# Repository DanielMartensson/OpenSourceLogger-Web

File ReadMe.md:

# OpenSourceLogger

This software creates a web application with Spring Boot and with this web application you can control and measure analog inputs and outputs and 
store them into a MySQL database.

# Features

* 4 Analog inputs of 12-bit
* 2 Analog inputs of 16-bit
* 3 Analog inputs of 16-bit differential
* 9 PWM control outputs
* 6 Digital inputs
* 3 Analog outputs of 12-bit
* Circuit protection from high voltage
* Spring Security Login
* MySQL database
* USB Camera view (Does not work with Raspberry Pi)
* Plotting functionality
* SMTP alarm functionality
* CSV generation of measurements
* Connect with RX and TX from Raspberry Pi pins
* Save unsaved database measurement for later if database might be slow for a moment
* Close down PWM and analog outputs when stop logging or alarm goes of

With this user view, you can control PWM, DAC, read ADC and logging digital inputs online over the web.
Set an alarm and calibration of a special sensor you want to use. Store all data inside the database. 
Then later you can bring the measurement back to a plot. Notice that you can close down the web browser while you logging.
It will continue to sample in a separate thread. 

This is made in KiCad. I have drag all the tracks on the board by my self. No auto-routing here.

I have solder all components by my self.

I have solder this microcontroller by hand. 

Applied inside a metallic box. Here I'm using Raspberry Pi to communicate with the board.
You can use a regular computer as well, as long you have a USB to serial converter, e.g `USB/UART converter FTDI FT232` where you connect `RXD -> TX` and `TXD -> RX` on the board.

# How to install - Ubuntu user

1. Install Java 11, Maven, NodeJS

Java 11
```
sudo apt-get install openjdk-11-jdk
```

Maven
```
sudo apt-get install maven
```

NodeJS
```
curl -sL https://deb.nodesource.com/setup_lts.x | sudo -E bash -
sudo apt-get install -y nodejs
```

2. Begin first to install MySQL Community Server

```
sudo apt-get install mysql-server
```

3. Then create a user e.g `myUser` with the password e.g `myPassword`

Login and enter your `sudo` password or mysql `root` password
```
sudo mysql -u root -p
```

Create user with the host `%` <-- That's important if you want to access your server from other computers.
```
CREATE USER 'myUser'@'%' IDENTIFIED BY 'myPassword';
```

Set the privileges to that user
```
GRANT ALL PRIVILEGES ON *.* TO 'myUser'@'%';
```

4. Change your MySQL server so you listening to your LAN address

Open this file
```
/etc/mysql/mysql.conf.d/mysqld.conf
```

And change this
```
bind-address            = 127.0.0.1
```

To your LAN address where the server is installed on e.g
```
bind-address            = 192.168.1.34
```

Then restart your MySQL server
```
sudo /etc/init.d/mysql restart
```

If you don't know your LAN address, you can type in this command in linux `ifconfig` in the terminal

5. Download `OpenSourceLogger`

Download the `OpenSourceLogger` and change the `application.properties` in the `/src/main/resources` folder.
Here you can set the configuration for your database IP address, user and password. Here set the address of your `Outlook` account.
The `service.MailService.from` must be the same as `configuration.MailConfiguration.username`.

```
# Database
spring.jpa.show-sql=true
spring.jpa.hibernate.ddl-auto=update
spring.jpa.properties.hibernate.dialect=org.hibernate.dialect.MySQL5Dialect
spring.datasource.url=jdbc:mysql://yourIPAddressOfTheServerWhereMySQLIsInstalled:3306/OpenSourceLogger?createDatabaseIfNotExist=true&serverTimezone=CET
spring.datasource.username=myUser
spring.datasource.password=myPassword

# Mail - Transmitter
configuration.MailConfiguration.host=smtp.office365.com
configuration.MailConfiguration.port=587
configuration.MailConfiguration.username=yourOutlookAccount@outlook.com
configuration.MailConfiguration.password=yourOutlookPassword

# Mail - Receiver
service.MailService.subject=Alarm Message Subject Title
service.MailService.from=yourOutlookAccount@outlook.com

# Login
spring.security.user.name=myUser
spring.security.user.password=myPassword
```

6. Pack this project and run

First stand inside of the folder `OpenSourceLogger` and write inside your terminal
```
mvn package -Pproduction
```

7. Starting the application

Now a JAR file is created inside the `OpenSourceLogger/target` folder. 

You can start `opensourcelogger-1.0-SNAPSHOT.jar`. First plugin your Serial UART into your USB port first, then write. 

```
sudo java -jar opensourcelogger-1.0-SNAPSHOT.jar
```

Once the application is started. You can then enter the web application e.g.

```
http://192.168.1.35:8080
```
Notice that there is no `https`, only `http`.

# Deploy onto Raspberry Pi

Notice that camera won't work on Raspberry Pi due to the latest library from [Sarox](https://github.com/sarxos/webcam-capture) cannot support Raspberry Pi 4B. But you can 
do everything else. If you want to work with this camera stuff inside `OpenSourceLogger`, please go to `CameraThread.java` class and begin to explore how to solve that problem.

Anyway! Once you got `opensourcelogger-1.0-SNAPSHOT.jar` ready, you can send it to your Raspberry Pi.

```
sudo scp opensourcelogger-1.0-SNAPSHOT.jar pi@RaspberryPiIPAddress:/The/Place/You/Want/The/Jar/File/To/Be/Saved
```

Example:

```
sudo scp opensourcelogger-1.0-SNAPSHOT.jar pi@192.168.1.35:/home/pi
```

Then open `rc.local`

```
sudo nano /etc/rc.local
```

And place these line above `exit 0`

```
cd /The/Path/To/Where/The/Jar/File/Is/Placed
sudo java -jar opensourcelogger-1.0-SNAPSHOT.jar &
```
Or if you want to specify the Java Heap Space for e.g `1024` Megabyte. Can be good if you want to download `.csv` data from the database.
```
cd /The/Path/To/Where/The/Jar/File/Is/Placed
sudo java -Xmx1024m -jar opensourcelogger-1.0-SNAPSHOT.jar &
```

Important with `&`, else Raspberry Pi is going to get stuck there with the `Spring Boot` terminal at the startup.

Then you need to enable `Serial` in Raspberry Pi.
```
sudo raspi-config
```
Then enable `Serial`. It's at the same page where you enable `SSH`, `VNC`, `I2C` etc. 
Once you found `Serial` option, answer `NO` to the question about login shell.
Then answer `YES` to the question about serial hardware port.
Then when you exit the `raspi-config`, it will ask you if you want to reboot, press `YES`

Now your `OpenSourceLogger` will starts automatically. Select the port `ttyS0` in `Device settings` at `OpenSourceLogger` and save the configuration
inside the database. `ttyS0` is the `RX` and `TX` pins of the Raspberry Pi. Done!

# Build an own board

Download `DAC ADC PWM IO - Board Schematic` and `DAC ADC PWM IO - STM32 Code` folder.
Inside the `DAC ADC PWM IO - Board Schematic` folder, there is a `.csv` Bill Of Materials list with article numbers from Mouser Electronics. 
I have been using `KiCad` to create these files and I used `https://jlcpcb.com` to give them the `gerber` files from the `DAC ADC PWM IO - Board Schematic` folder.

To program the board, use a `ST-LINK-V2` programmer to program the board with `STM32CubeIDE 1.5.0`.

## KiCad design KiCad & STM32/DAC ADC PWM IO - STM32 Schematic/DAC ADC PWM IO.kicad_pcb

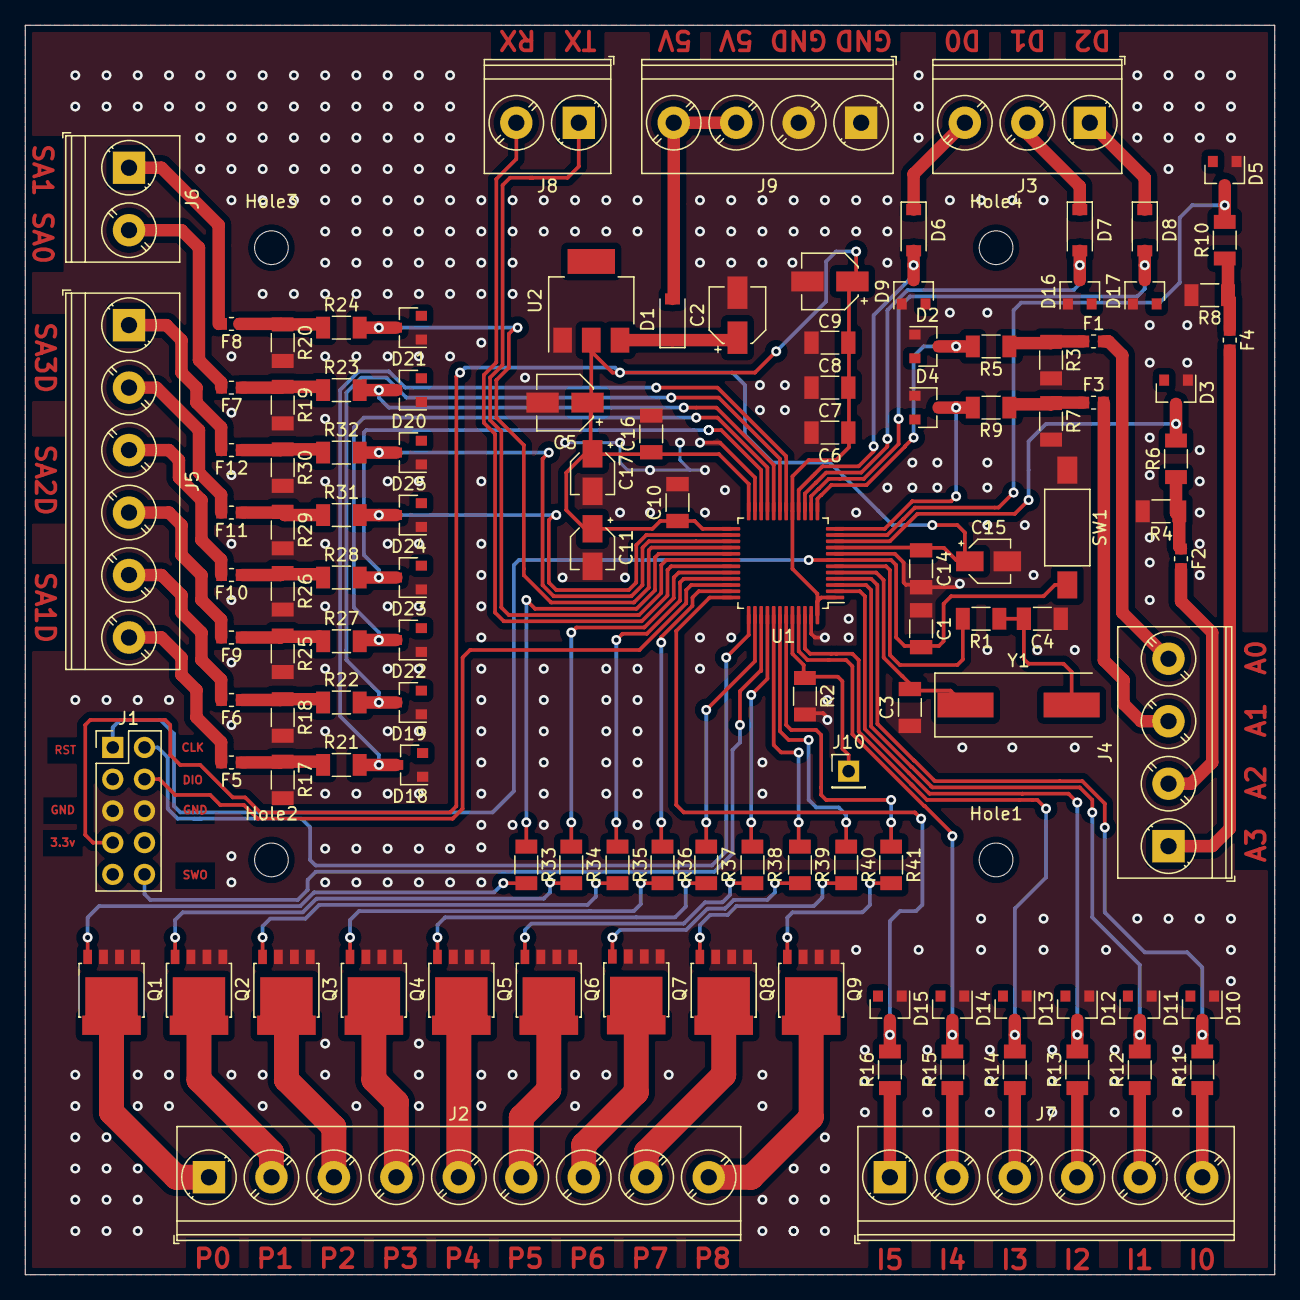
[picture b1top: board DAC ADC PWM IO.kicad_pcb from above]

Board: 2 copper layers, 100.0 x 100.0 mm, 120 parts (0 on the bottom side), 95 nets.

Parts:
C1, C6, C7, C8: 100nF; C_1206_3216Metric
C2, C5: 10uF; CP_Elec_4x5.3
C3, C4: 16pF; C_1206_3216Metric
C9: 4.7uF; CP_Elec_4x5.4
C10, C14, C16: 10nF; C_1206_3216Metric
C11, C15, C17: 1uF; CP_Elec_3x5.4
D1: MBR130T1G; D_SOD-123
D2, D3, D4, D5, D9, D10, D11, D12, D13, D14, D15, D16, D17, D18, D19, D20, D21, D22, D23, D24, D25: BZX84C3V6LT1G; D_SOT-23_ANK
D6, D7, D8: BAT54T1G; D_SOD-123
F1, F2, F3, F4, F5, F6, F7, F8, F9, F10, F11, F12: Polyfuse; Fuse_0603_1608Metric
Hole1, Hole2, Hole3, Hole4: MountingHole_2.7mm
J1: Debugger; PinHeader_2x05_P2.54mm_Vertical
J2: PWM; TerminalBlock_Phoenix_PT-1,5-9-5.0-H_1x09_P5.00mm_Horizontal
J3: DAC; TerminalBlock_Phoenix_PT-1,5-3-5.0-H_1x03_P5.00mm_Horizontal
J4: 4-20mA 12-bit; TerminalBlock_Phoenix_PT-1,5-4-5.0-H_1x04_P5.00mm_Horizontal
J5: 4-20mA 16-bit Differential; TerminalBlock_Phoenix_PT-1,5-6-5.0-H_1x06_P5.00mm_Horizontal
J6: 4-20mA 16-bit; TerminalBlock_Phoenix_PT-1,5-2-5.0-H_1x02_P5.00mm_Horizontal
J7: Input; TerminalBlock_Phoenix_PT-1,5-6-5.0-H_1x06_P5.00mm_Horizontal
J8: UART; TerminalBlock_Phoenix_PT-1,5-2-5.0-H_1x02_P5.00mm_Horizontal
J9: PWR; TerminalBlock_Phoenix_PT-1,5-4-5.0-H_1x04_P5.00mm_Horizontal
J10: Conn_01x01_MountingPin; PinHeader_1x01_P2.54mm_Vertical
Q1, Q2, Q3, Q4, Q5, Q6, Q7, Q8, Q9: BUK9Y43-60E,115; LFPAK56
R1: 620; R_1206_3216Metric
R2, R11, R12, R13, R14, R15, R16: 10k; R_1206_3216Metric
R3, R4, R7, R8, R17, R18, R19, R20, R25, R26, R29, R30: 150; R_1206_3216Metric
R5, R6, R9, R10, R21, R22, R23, R24, R27, R28, R31, R32: 2k; R_1206_3216Metric
R33, R34, R35, R36, R37, R38, R39, R40, R41: 1k; R_1206_3216Metric
SW1: SW_Push; SW_SPST_FSMSM
U1: STM32F373CCT6; LQFP-48_7x7mm_P0.5mm
U2: LM1117-3.3; SOT-223
Y1: 16Mhz, 18pF; Crystal_SMD_HC49-SD

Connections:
+3V3: C5.1, C6.1, C7.1, C8.1, C9.1, C10.1, C11.1, C14.1, C15.1, C16.1, C17.1, J1.7, U1.1, U1.9, U1.17, U1.24, U1.25, U1.48, U2.2
+5V: D1.2, J9.3, J9.4
/ADC/ADC0: F1.2, J4.4
/ADC/ADC1: F3.2, J4.3
/ADC/ADC2: F2.2, J4.2
/ADC/ADC3: F4.2, J4.1
/BOOT0: J10.1, R2.1, U1.44
/DAC/DAC0: D6.1, J3.3
/DAC/DAC1: D7.1, J3.2
/DAC/DAC2: D8.1, J3.1
/INPUT/INPUT0: J7.6, R11.1
/INPUT/INPUT1: J7.5, R12.1
/INPUT/INPUT2: J7.4, R13.1
/INPUT/INPUT3: J7.3, R14.1
/INPUT/INPUT4: J7.2, R15.1
/INPUT/INPUT5: J7.1, R16.1
/NRST: C1.2, J1.1, SW1.2, U1.7
/PA0: D3.1, R6.2, U1.10
/PA1: D5.1, R10.2, U1.11
/PA2: D4.1, R9.2, U1.12
/PA3: D2.1, R5.2, U1.13
/PA4: D8.2, D17.1, U1.14
/PA5: D7.2, D16.1, U1.15
/PA6: D6.2, D9.1, U1.16
/PA8: R33.1, U1.29
/PA9: J8.1, U1.30
/PA10: J8.2, U1.31
/PA11: R34.1, U1.32
/PA12: R35.1, U1.33
/PA13: J1.4, U1.34
/PA14: J1.2, U1.37
/PA15: R37.1, U1.38
/PB0: D18.1, R21.2, U1.18
/PB1: D19.1, R22.2, U1.19
/PB2: D20.1, R23.2, U1.20
/PB3: J1.10, U1.39
/PB4: R38.1, U1.40
/PB5: R39.1, U1.41
/PB6: R40.1, U1.42
/PB7: R41.1, U1.43
/PB8: D14.1, R15.2, U1.45
/PB9: D13.1, R14.2, U1.46
/PB14: D24.1, R31.2, U1.26
/PB15: D25.1, R32.2, U1.27
/PC13: D12.1, R13.2, U1.2
/PC14: D11.1, R12.2, U1.3
/PC15: D10.1, R11.2, U1.4
/PD8: D21.1, R24.2, U1.28
/PE8: D22.1, R27.2, U1.21
/PE9: D23.1, R28.2, U1.22
/PF0: C3.2, U1.5, Y1.1
/PF1: R1.2, U1.6
/PF6: R36.1, U1.35
/PF7: D15.1, R16.2, U1.36
/PWM/PWM0: J2.1, Q1.5
/PWM/PWM1: J2.2, Q2.5
/PWM/PWM2: J2.3, Q3.5
/PWM/PWM3: J2.4, Q4.5
/PWM/PWM4: J2.5, Q5.5
/PWM/PWM5: J2.6, Q6.5
/PWM/PWM6: J2.7, Q7.5
/PWM/PWM7: J2.8, Q8.5
/PWM/PWM8: J2.9, Q9.5
/SDADC/SDADC0M: F6.2, J5.5
/SDADC/SDADC0P: F5.2, J5.6
/SDADC/SDADC1: F7.2, J6.2
/SDADC/SDADC2: F8.2, J6.1
/SDADC/SDADC2M: F10.2, J5.3
/SDADC/SDADC2P: F9.2, J5.4
/SDADC/SDADC3M: F12.2, J5.1
/SDADC/SDADC3P: F11.2, J5.2
GND: C1.1, C2.2, C3.1, C4.1, C5.2, C6.2, C7.2, C8.2, C9.2, C10.2, C11.2, C14.2, C15.2, C16.2, C17.2, D2.2, D3.2, D4.2, D5.2, D9.2, D10.2, D11.2, D12.2, D13.2, D14.2, D15.2, D16.2, D17.2, D18.2, D19.2, D20.2, D21.2, D22.2, D23.2, D24.2, D25.2, J1.5, J1.6, J9.1, J9.2, Q1.1, Q1.2, Q1.3, Q2.1, Q2.2, Q2.3, Q3.1, Q3.2, Q3.3, Q4.1, Q4.2, Q4.3, Q5.1, Q5.2, Q5.3, Q6.1, Q6.2, Q6.3, Q7.1, Q7.2, Q7.3, Q8.1, Q8.2, Q8.3, Q9.1, Q9.2, Q9.3, R2.2, R3.2, R4.2, R7.2, R8.2, R17.2, R18.2, R19.2, R20.2, R25.2, R26.2, R29.2, R30.2, SW1.1, U1.8, U1.23, U1.47, U2.1
unnamed: C2.1, D1.1, U2.3
unnamed: C4.2, R1.1, Y1.2
unnamed: F1.1, R3.1, R5.1
unnamed: F2.1, R4.1, R6.1
unnamed: F3.1, R7.1, R9.1
unnamed: F4.1, R8.1, R10.1
unnamed: F5.1, R17.1, R21.1
unnamed: F6.1, R18.1, R22.1
unnamed: F7.1, R19.1, R23.1
unnamed: F8.1, R20.1, R24.1
unnamed: F9.1, R25.1, R27.1
unnamed: F10.1, R26.1, R28.1
unnamed: F11.1, R29.1, R31.1
unnamed: F12.1, R30.1, R32.1
unnamed: Q1.4, R33.2
unnamed: Q2.4, R34.2
unnamed: Q3.4, R35.2
unnamed: Q4.4, R36.2
unnamed: Q5.4, R37.2
unnamed: Q6.4, R38.2
unnamed: Q7.4, R39.2
unnamed: Q8.4, R40.2
unnamed: Q9.4, R41.2

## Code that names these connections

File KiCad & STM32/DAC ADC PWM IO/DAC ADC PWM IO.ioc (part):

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Mcu.Name=STM32F373C(8-B-C)Tx
Mcu.Package=LQFP48
Mcu.UserName=STM32F373CCTx
PA0.Mode=IN0
PA0.Signal=ADC1_IN0
PA1.Mode=IN1
PA1.Signal=ADC1_IN1
PA10.Mode=Asynchronous
PA10.Signal=USART1_RX
PA11.Signal=S_TIM5_CH2
PA12.Signal=S_TIM5_CH3
PA13.Mode=Trace_Asynchronous_SW
PA13.Signal=SYS_JTMS-SWDIO
PA14.Mode=Trace_Asynchronous_SW
PA14.Signal=SYS_JTCK-SWCLK
PA15.Signal=S_TIM2_CH1_ETR
PA2.Mode=IN2
PA2.Signal=ADC1_IN2
PA3.Mode=IN3
PA3.Signal=ADC1_IN3
PA4.Signal=COMP_DAC11_group
PA5.Signal=COMP_DAC12_group
PA6.Signal=COMP_DAC21_group
PA8.Signal=S_TIM5_CH1_ETR
PA9.Mode=Asynchronous
PA9.Signal=USART1_TX
PB0.Mode=IN6-Differential
PB0.Signal=SDADC1_AIN6P
PB1.Mode=IN6-Differential
PB1.Signal=SDADC1_AIN6M
PB14.Mode=IN8-Differential
PB14.Signal=SDADC3_AIN8P
PB15.Mode=IN8-Differential
PB15.Signal=SDADC3_AIN8M
PB2.Mode=IN4-Single-Ended zero reference
PB2.Signal=SDADC1_AIN4P
PB3.Mode=Trace_Asynchronous_SW
PB3.Signal=SYS_JTDO-TRACESWO
PB4.Signal=S_TIM3_CH1
PB5.Signal=S_TIM3_CH2
PB6.Signal=S_TIM4_CH1
PB7.Signal=S_TIM4_CH2
PB8.GPIOParameters=GPIO_PuPd,GPIO_Label
PB8.GPIO_Label=INPUT 4
PB8.GPIO_PuPd=GPIO_PULLDOWN
PB8.Signal=GPIO_Input
PB9.GPIOParameters=GPIO_PuPd,GPIO_Label
PB9.GPIO_Label=INPUT 3
PB9.GPIO_PuPd=GPIO_PULLDOWN
PB9.Signal=GPIO_Input
PC13.GPIOParameters=GPIO_PuPd,GPIO_Label
PC13.GPIO_Label=INPUT 2
PC13.GPIO_PuPd=GPIO_PULLDOWN
PC13.Signal=GPIO_Input
PC14-OSC32_IN.GPIOParameters=GPIO_PuPd,GPIO_Label
PC14-OSC32_IN.GPIO_Label=INPUT 1
PC14-OSC32_IN.GPIO_PuPd=GPIO_PULLDOWN
PC14-OSC32_IN.Signal=GPIO_Input
PC15-OSC32_OUT.GPIOParameters=GPIO_PuPd,GPIO_Label
PC15-OSC32_OUT.GPIO_Label=INPUT 0
PC15-OSC32_OUT.GPIO_PuPd=GPIO_PULLDOWN
PC15-OSC32_OUT.Signal=GPIO_Input
PD8.Mode=IN6-Single-Ended zero reference
PD8.Signal=SDADC3_AIN6P
PE8.Mode=IN8-Differential
PE8.Signal=SDADC1_AIN8P
PE9.Mode=IN8-Differential
PE9.Signal=SDADC1_AIN8M
PF0-OSC_IN.Mode=HSE-External-Oscillator
PF0-OSC_IN.Signal=RCC_OSC_IN
PF1-OSC_OUT.Mode=HSE-External-Oscillator
PF1-OSC_OUT.Signal=RCC_OSC_OUT
PF6.Signal=S_TIM4_CH4
PF7.GPIOParameters=GPIO_PuPd,GPIO_Label
PF7.GPIO_Label=INPUT 5
PF7.GPIO_PuPd=GPIO_PULLDOWN
PF7.Signal=GPIO_Input
RCC.HSEPLLFreq_Value=16000000
RCC.HSE_VALUE=16000000
RCC.SYSCLKFreq_VALUE=16000000
RCC.SYSCLKSource=RCC_SYSCLKSOURCE_HSE
board=custom

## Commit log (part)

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2020-07-12 New init
2020-07-17 Update - Ready for testing
2020-08-17 New update
2020-10-05 Changed from GAIN_TWO to GAIN_ONE
2020-10-05 Changes insert for MySQL
2020-10-05 Batch sampling now
2020-10-05 New delete notification for Stack Overflow
2020-10-06 Fixed Download button
2020-10-06 Changed LocalDate to LocalDateTime
2020-10-06 Update all
2020-10-06 Implementing milliseconds in Entity
2020-10-06 Updated from GitHub
2020-10-06 Update MySQL view
2020-10-06 Correct order of data samples now
2020-10-06 Update Download Button
2020-11-09 News
2020-11-09 News and updates
2020-11-09 Update with explanations
2020-12-22 Bump ini from 1.3.5 to 1.3.8
    Bumps [ini](https://github.com/isaacs/ini) from 1.3.5 to 1.3.8.
    - [Release notes](https://github.com/isaacs/ini/releases)
    - [Commits](https://github.com/isaacs/ini/compare/v1.3.5...v1.3.8)
2020-12-22 Uploaded STM32 board and code
2020-12-23 Solution for Raspberry Pi
2020-12-23 Update for raspberry pi camera
2020-12-23 Update ish...
2020-12-23 Upload STM32 board and code
2020-12-23 Update instructions how to build the board
2020-12-23 Removed picture
2020-12-23 Update box picture
2020-12-23 Add Board PCB schematics and code
2020-12-23 Added more information how to enable S0
2020-12-23 Added STM32 files
2020-12-23 Misspell
2020-12-24 Fixed indexing
2020-12-24 Update and clean up
2020-12-25 Renamed
2020-12-25 Update. Found bugs. Solved issues...
2020-12-25 Removed a space
2020-12-25 For to From
2020-12-25 More information
2020-12-28 Found a better way to stop logging directly
2020-12-29 When we delete job, the corresponding data will also be removed
2020-12-29 New UI view
2020-12-29 Solved an issue about couted pulses
2020-12-29 Vaadin Update
2020-12-29 Clears array before receiving data
2020-12-29 Clear all int arrays
2020-12-29 16-bit ADC applied for single
2020-12-29 Changed 0-20mA to 0-22mA because I'm using 150 Ohm resistor
2020-12-30 New calibration manual
2020-12-30 Better size of the images
2021-01-02 Lower baudrate from 115200 to 9600
2021-01-03 Better communication with STM32
2021-01-03 Got a UIDetechedException
2021-01-03 When the alarm is active, then we have recieve the stopSignal variable to true
2021-01-03 Removes the curly blocks from single if-statement
2021-01-05 Offline sampling applied
2021-01-05 Implement safety features and database connection check
2021-01-05 Update dependencies
2021-01-05 Better code and easier to understand
2021-01-05 Update alarmService and calibrationService
2021-01-05 Possible to show one or multiple chart series now
2021-01-09 Big update 2 - Faster Database reading
2021-01-10 Update with step
2021-01-10 Euler simulation for first order state space equation, as filter
2021-01-10 Done with better MySQL reading
2021-01-10 Changed "Step index" to "Step index(plot only)"
2021-01-10 Renamed DateTime to LocalDateTime
2021-01-10 Update Vaadin
2021-01-10 Update to Long
2021-01-10 x -> ADC
2021-01-10 Change initial Euler filtering to 1.0
2021-01-10 Step index cannot be larger than last index
2021-01-10 Implements counter how many times we can write to database
2021-01-11 Update - Found a bug
2021-01-11 Better moving average
2021-01-11 Use static string fields as names for the fields in Data class
2021-01-12 Update class path
2021-01-13 Added Notification "Out of memory"
2021-01-13 Add comment to database and job
2021-01-13 Add comment field to JobView
2021-02-11 Bump apexcharts from 3.20.2 to 3.24.0
    Bumps [apexcharts](https://github.com/apexcharts/apexcharts.js) from 3.20.2 to 3.24.0.
    - [Release notes](https://github.com/apexcharts/apexcharts.js/releases)
    - [Commits](https://github.com/apexcharts/apexcharts.js/commits)
2021-02-23 Added @Transactional for deleteByJobName(String jobName)
    Got the error "No EntityManager with actual transaction available for current thread - cannot reliably process 'remove' call"
2021-02-24 Added a Query for deleteByJobName
    I hope this should be faster!
2021-04-19 Bump vaadin.version from 14.4.5 to 19.0.5
    Bumps `vaadin.version` from 14.4.5 to 19.0.5.
    Updates `vaadin-bom` from 14.4.5 to 19.0.5
    Updates `vaadin-maven-plugin` from 14.4.5 to 19.0.5
2021-04-20 Bump ssri from 6.0.1 to 6.0.2
    Bumps [ssri](https://github.com/npm/ssri) from 6.0.1 to 6.0.2.
    - [Release notes](https://github.com/npm/ssri/releases)
    - [Changelog](https://github.com/npm/ssri/blob/v6.0.2/CHANGELOG.md)
    - [Commits](https://github.com/npm/ssri/compare/v6.0.1...v6.0.2)
2021-04-22 Bump elliptic from 6.5.3 to 6.5.4
    Bumps [elliptic](https://github.com/indutny/elliptic) from 6.5.3 to 6.5.4.
    - [Release notes](https://github.com/indutny/elliptic/releases)
    - [Commits](https://github.com/indutny/elliptic/compare/v6.5.3...v6.5.4)
2021-05-06 Bump vaadin.version from 14.4.5 to 19.0.6
    Bumps `vaadin.version` from 14.4.5 to 19.0.6.
    Updates `vaadin-bom` from 14.4.5 to 19.0.6
    Updates `vaadin-maven-plugin` from 14.4.5 to 19.0.6
2021-05-11 Bump lodash from 4.17.20 to 4.17.21
    Bumps [lodash](https://github.com/lodash/lodash) from 4.17.20 to 4.17.21.
    - [Release notes](https://github.com/lodash/lodash/releases)
    - [Commits](https://github.com/lodash/lodash/compare/4.17.20...4.17.21)
2021-05-26 Bump browserslist from 4.16.0 to 4.16.6
    Bumps [browserslist](https://github.com/browserslist/browserslist) from 4.16.0 to 4.16.6.
    - [Release notes](https://github.com/browserslist/browserslist/releases)
    - [Changelog](https://github.com/browserslist/browserslist/blob/main/CHANGELOG.md)
    - [Commits](https://github.com/browserslist/browserslist/compare/4.16.0...4.16.6)
2021-05-29 Bump dns-packet from 1.3.1 to 1.3.4
    Bumps [dns-packet](https://github.com/mafintosh/dns-packet) from 1.3.1 to 1.3.4.
    - [Release notes](https://github.com/mafintosh/dns-packet/releases)
    - [Changelog](https://github.com/mafintosh/dns-packet/blob/master/CHANGELOG.md)
    - [Commits](https://github.com/mafintosh/dns-packet/compare/v1.3.1...v1.3.4)
2021-06-23 Update pom.xml
    dff
2021-06-28 Bump vaadin-bom from 14.4.5 to 14.6.2
    Bumps vaadin-bom from 14.4.5 to 14.6.2.
    ---
    updated-dependencies:
    - dependency-name: com.vaadin:vaadin-bom
    dependency-type: direct:production
    ...
2021-08-04 Bump tar from 6.0.5 to 6.1.5
    Bumps [tar](https://github.com/npm/node-tar) from 6.0.5 to 6.1.5.
    - [Release notes](https://github.com/npm/node-tar/releases)
    - [Changelog](https://github.com/npm/node-tar/blob/main/CHANGELOG.md)
    - [Commits](https://github.com/npm/node-tar/compare/v6.0.5...v6.1.5)
    ---
    updated-dependencies:
2021-08-30 Bump vaadin-bom from 14.4.5 to 14.6.8
    Bumps vaadin-bom from 14.4.5 to 14.6.8.
    ---
    updated-dependencies:
    - dependency-name: com.vaadin:vaadin-bom
    dependency-type: direct:production
    ...
2021-09-03 Bump url-parse from 1.4.7 to 1.5.3
    Bumps [url-parse](https://github.com/unshiftio/url-parse) from 1.4.7 to 1.5.3.
    - [Release notes](https://github.com/unshiftio/url-parse/releases)
    - [Commits](https://github.com/unshiftio/url-parse/compare/1.4.7...1.5.3)
    ---
    updated-dependencies:
    - dependency-name: url-parse
2022-01-15 Bump follow-redirects from 1.13.1 to 1.14.7
    Bumps [follow-redirects](https://github.com/follow-redirects/follow-redirects) from 1.13.1 to 1.14.7.
    - [Release notes](https://github.com/follow-redirects/follow-redirects/releases)
    - [Commits](https://github.com/follow-redirects/follow-redirects/compare/v1.13.1...v1.14.7)
    ---
    updated-dependencies:
    - dependency-name: follow-redirects
2022-02-13 Bump follow-redirects from 1.13.1 to 1.14.8
    Bumps [follow-redirects](https://github.com/follow-redirects/follow-redirects) from 1.13.1 to 1.14.8.
    - [Release notes](https://github.com/follow-redirects/follow-redirects/releases)
    - [Commits](https://github.com/follow-redirects/follow-redirects/compare/v1.13.1...v1.14.8)
    ---
    updated-dependencies:
    - dependency-name: follow-redirects
2022-02-19 Bump url-parse from 1.4.7 to 1.5.7
    Bumps [url-parse](https://github.com/unshiftio/url-parse) from 1.4.7 to 1.5.7.
    - [Release notes](https://github.com/unshiftio/url-parse/releases)
    - [Commits](https://github.com/unshiftio/url-parse/compare/1.4.7...1.5.7)
    ---
    updated-dependencies:
    - dependency-name: url-parse
2022-03-28 Bump minimist from 1.2.5 to 1.2.6
    Bumps [minimist](https://github.com/substack/minimist) from 1.2.5 to 1.2.6.
    - [Release notes](https://github.com/substack/minimist/releases)
    - [Commits](https://github.com/substack/minimist/compare/1.2.5...1.2.6)
    ---
    updated-dependencies:
    - dependency-name: minimist
2022-04-29 Bump async from 2.6.3 to 2.6.4
    Bumps [async](https://github.com/caolan/async) from 2.6.3 to 2.6.4.
    - [Release notes](https://github.com/caolan/async/releases)
    - [Changelog](https://github.com/caolan/async/blob/v2.6.4/CHANGELOG.md)
    - [Commits](https://github.com/caolan/async/compare/v2.6.3...v2.6.4)
    ---
    updated-dependencies:
2022-06-01 Bump eventsource from 1.0.7 to 1.1.1
    Bumps [eventsource](https://github.com/EventSource/eventsource) from 1.0.7 to 1.1.1.
    - [Release notes](https://github.com/EventSource/eventsource/releases)
    - [Changelog](https://github.com/EventSource/eventsource/blob/master/HISTORY.md)
    - [Commits](https://github.com/EventSource/eventsource/compare/v1.0.7...v1.1.1)
    ---
    updated-dependencies:
2022-11-08 Bump loader-utils, webpack-cli and webpack-babel-multi-target-plugin
    Bumps [loader-utils](https://github.com/webpack/loader-utils) to 1.4.1 and updates ancestor dependencies [loader-utils](https://github.com/webpack/loader-utils), [webpack-cli](https://github.com/webp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
    Updates `loader-utils` from 1.4.0 to 1.4.1
    - [Release notes](https://github.com/webpack/loader-utils/releases)
    - [Changelog](https://github.com/webpack/loader-utils/blob/v1.4.1/CHANGELOG.md)
    - [Commits](https://github.com/webpack/loader-utils/compare/v1.4
2022-11-10 Bump minimatch from 3.0.4 to 3.1.2
    Bumps [minimatch](https://github.com/isaacs/minimatch) from 3.0.4 to 3.1.2.
    - [Release notes](https://github.com/isaacs/minimatch/releases)
    - [Commits](https://github.com/isaacs/minimatch/compare/v3.0.4...v3.1.2)
    ---
    updated-dependencies:
    - dependency-name: minimatch
2022-11-21 Bump loader-utils, webpack-cli and webpack-babel-multi-target-plugin
    Bumps [loader-utils](https://github.com/webpack/loader-utils) to 1.4.2 and updates ancestor dependencies [loader-utils](https://github.com/webpack/loader-utils), [webpack-cli](https://github.com/webp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
    Updates `loader-utils` from 1.4.0 to 1.4.2
    - [Release notes](https://github.com/webpack/loader-utils/releases)
    - [Changelog](https://github.com/webpack/loader-utils/blob/v1.4.2/CHANGELOG.md)
    - [Commits](https://github.com/webpack/loader-utils/compare/v1.4
2022-12-07 Bump decode-uri-component from 0.2.0 to 0.2.2
    Bumps [decode-uri-component](https://github.com/SamVerschueren/decode-uri-component) from 0.2.0 to 0.2.2.
    - [Release notes](https://github.com/SamVerschueren/decode-uri-component/releases)
    - [Commits](https://github.com/SamVerschueren/decode-uri-component/compare/v0.2.0...v0.2.2)
    ---
    updated-dependencies:
    - dependency-name: decode-uri-component
2022-12-13 Bump express from 4.17.1 to 4.18.2
    Bumps [express](https://github.com/expressjs/express) from 4.17.1 to 4.18.2.
    - [Release notes](https://github.com/expressjs/express/releases)
    - [Changelog](https://github.com/expressjs/express/blob/master/History.md)
    - [Commits](https://github.com/expressjs/express/compare/4.17.1...4.18.2)
    ---
    updated-dependencies:
